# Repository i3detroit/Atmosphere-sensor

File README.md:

# Atmosphere-sensor
board files, old custom code, enclosure files, tasmota config files, all relating to our atmosphere cluster boards

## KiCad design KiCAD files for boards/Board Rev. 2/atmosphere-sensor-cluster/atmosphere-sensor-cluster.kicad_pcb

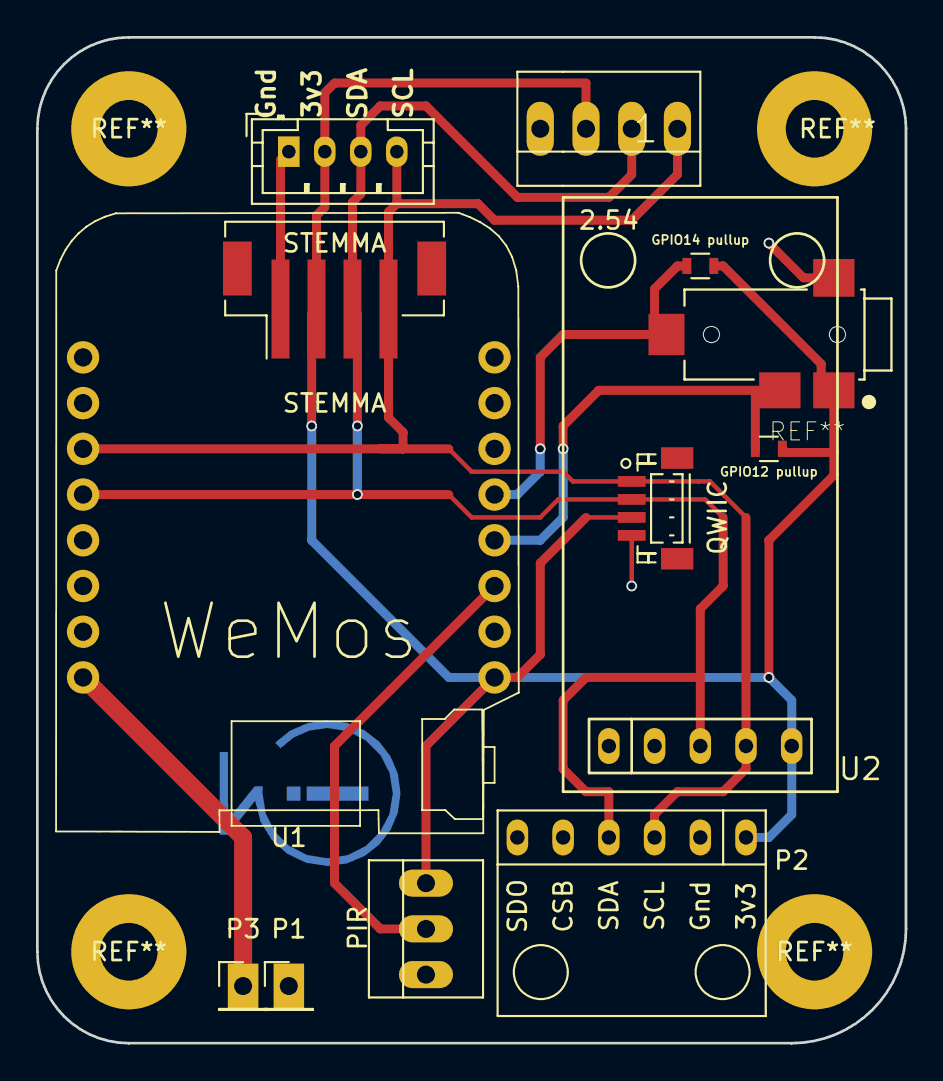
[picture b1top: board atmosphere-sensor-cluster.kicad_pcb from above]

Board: 2 copper layers, 48.3 x 55.9 mm, 13 parts (1 on the bottom side), 8 nets.

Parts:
2.54: PINHEAD1-4
GPIO12 pullup, GPIO14 pullup: R_0603
P1, P3: CONN_01X01; Pin_Header_Straight_1x01_Pitch2.54mm
P2: bme280; BMP280W
PIR: PINHEAD1-3
QWIIC: QWIIC; JST_SH_BM04B-SRSS-TB_04x1.00mm_Straight
STEMMA: stemma; JST_PH_B4B-PH-K_04x2.00mm_Straight
STEMMA#2: JST PH I2C; JST_PH_B4B-PH-SM4-TB_04x2.00mm_Straight
U1: WeMos_mini; D1_mini_board
U2: BHT1750
i3Detroit: i3Logo1cm

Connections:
+3V3: 2.54.3, GPIO12 pullup.2, GPIO14 pullup.2, P2.1, PIR.3, QWIIC.3, STEMMA.2, STEMMA#2.2, U1.16, U2.5
+5V: P3.1, U1.1
/GPIO12: GPIO12 pullup.1, U1.13
/GPIO14: GPIO14 pullup.1, U1.12
/PIR: PIR.2, U1.14
/SCL: 2.54.1, P2.3, QWIIC.1, STEMMA.4, STEMMA#2.4, U1.6, U2.4
/SDA: 2.54.2, P2.4, QWIIC.2, STEMMA.3, STEMMA#2.3, U1.5, U2.3
GND: 2.54.4, P1.1, P2.2, PIR.1, QWIIC.4, STEMMA.1, STEMMA#2.1, U1.2, U2.1, U2.2

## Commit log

2021-01-23 added old files from custom programs repo
2021-01-23 added rev2 kicad board
